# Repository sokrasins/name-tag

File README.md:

# MAKE Roanoke Name tag

A battery-powered, LED-lit "My name is" name tag for
MAKE Roanoke, designed in KiCad 9.

It is made of two stacked PCBs:

- **Back board:** holds all the electronics, including the battery, power
  switch, boost converter, brightness pot and 27 LEDs. This board provides 
  illumination to highlight the features on the front board.
- **Front board:** a plain faceplate with no parts. It has the "My name is:"
  silkscreen and a wrench graphic, and it covers the LED area of the back 
  board. The board lacks soldermask so that the wrench and the area with the 
  individual's name light up when the name tag is on.

The boards line up on four M3 mounting holes and are held together with
standoffs. A slot at the top of the back board is for a clip.

This project has been designed explicitly to be built via reflow as part of a 
class.

Viewable links are here:
- [Schematic](https://github.com/sokrasins/nametag/blob/main/docs/nametag_back_schematic_rev2.pdf)
- [Back PCB](https://pcbview.io/?github=https%3A%2F%2Fgithub.com%2Fsokrasins%2Fname-tag%2Fblob%2FHEAD%2Fpcbs%2Fnametag_back%2Fnametag_back.kicad_pcb)
- [Front PCB](https://pcbview.io/?github=https%3A%2F%2Fgithub.com%2Fsokrasins%2Fname-tag%2Fblob%2FHEAD%2Fpcbs%2Fnametag_front%2Fnametag_front.kicad_pcb)
- [Assembly](https://htmlpreview.github.io/?https://raw.githubusercontent.com/sokrasins/nametag/refs/heads/develop/docs/assembly.html)

## Renders

## How it works

- **Power:** a single AAA cell switched by an SPDT slide switch.
- **Boost converter:** a TI TPS613221A steps the cell up to a +3V3 rail.
- **LEDs:** 27× SMD LEDs (22 yellow, 5 green). Each one has a 1 kΩ
  current-limiting resistor.
- **Brightness:** all LEDs share a single BSS138 low-side MOSFET. A 10 kΩ
  Bourns TC33X trimmer potentiometer divides the 3.3 V rail and drives its
  `CTRL` gate line, so turning it dims or brightens every LED together.

## Boards

| | Back | Front |
| --- | --- | --- |
| Size | 100 × 75 mm | 100 × 53 mm |
| Layers / thickness | 2 / 1.6 mm | 2 / 1.6 mm |
| Components | All electronics | None (4× M3 holes) |

## Repository layout

| Path | Contents |
| --- | --- |
| `pcbs/nametag_back/` | Back board KiCad project (schematic and layout) |
| `pcbs/nametag_back/gerbs/` | Back board Gerbers and drill files |
| `pcbs/nametag_front/` | Front board KiCad project (layout only, no schematic) |
| `pcbs/nametag_front/gerbs/` | Front board Gerbers and drill files |
| `docs/assembly.html` | Interactive BOM for assembling the back board |
| `docs/bom.csv` | Bill of materials for the back board, with LCSC part numbers |

## Regenerating the renders, schematic PDF and interactive BOM

With KiCad 9 or newer installed, run:

```sh
scripts/render_pcbs.sh          # top side (the images above)
scripts/render_pcbs.sh both     # also writes docs/renders/*_render_bottom.png
```

It calls `kicad-cli pcb render` for each board and `kicad-cli sch export pdf`
to write `docs/nametag_back_schematic_rev<N>.pdf`, where `<N>` is the
revision from the schematic's title block. Set `KICAD_CLI` if
`kicad-cli` isn't on your `PATH`. `QUALITY`, `WIDTH`, `HEIGHT` and `BACKGROUND`
change the output.

If the [InteractiveHtmlBom](https://github.com/openscopeproject/InteractiveHtmlBom)
plugin is installed through KiCad's Plugin and Content Manager, it also writes
`docs/assembly.html`. Set `IBOM` to point at `generate_interactive_bom.py` if
the plugin lives elsewhere, and `IBOM_PYTHON` if the python that can import
KiCad's `pcbnew` module isn't found automatically.

## Open items

- The top-level schematic still has a couple of "TODO: Verify" notes.

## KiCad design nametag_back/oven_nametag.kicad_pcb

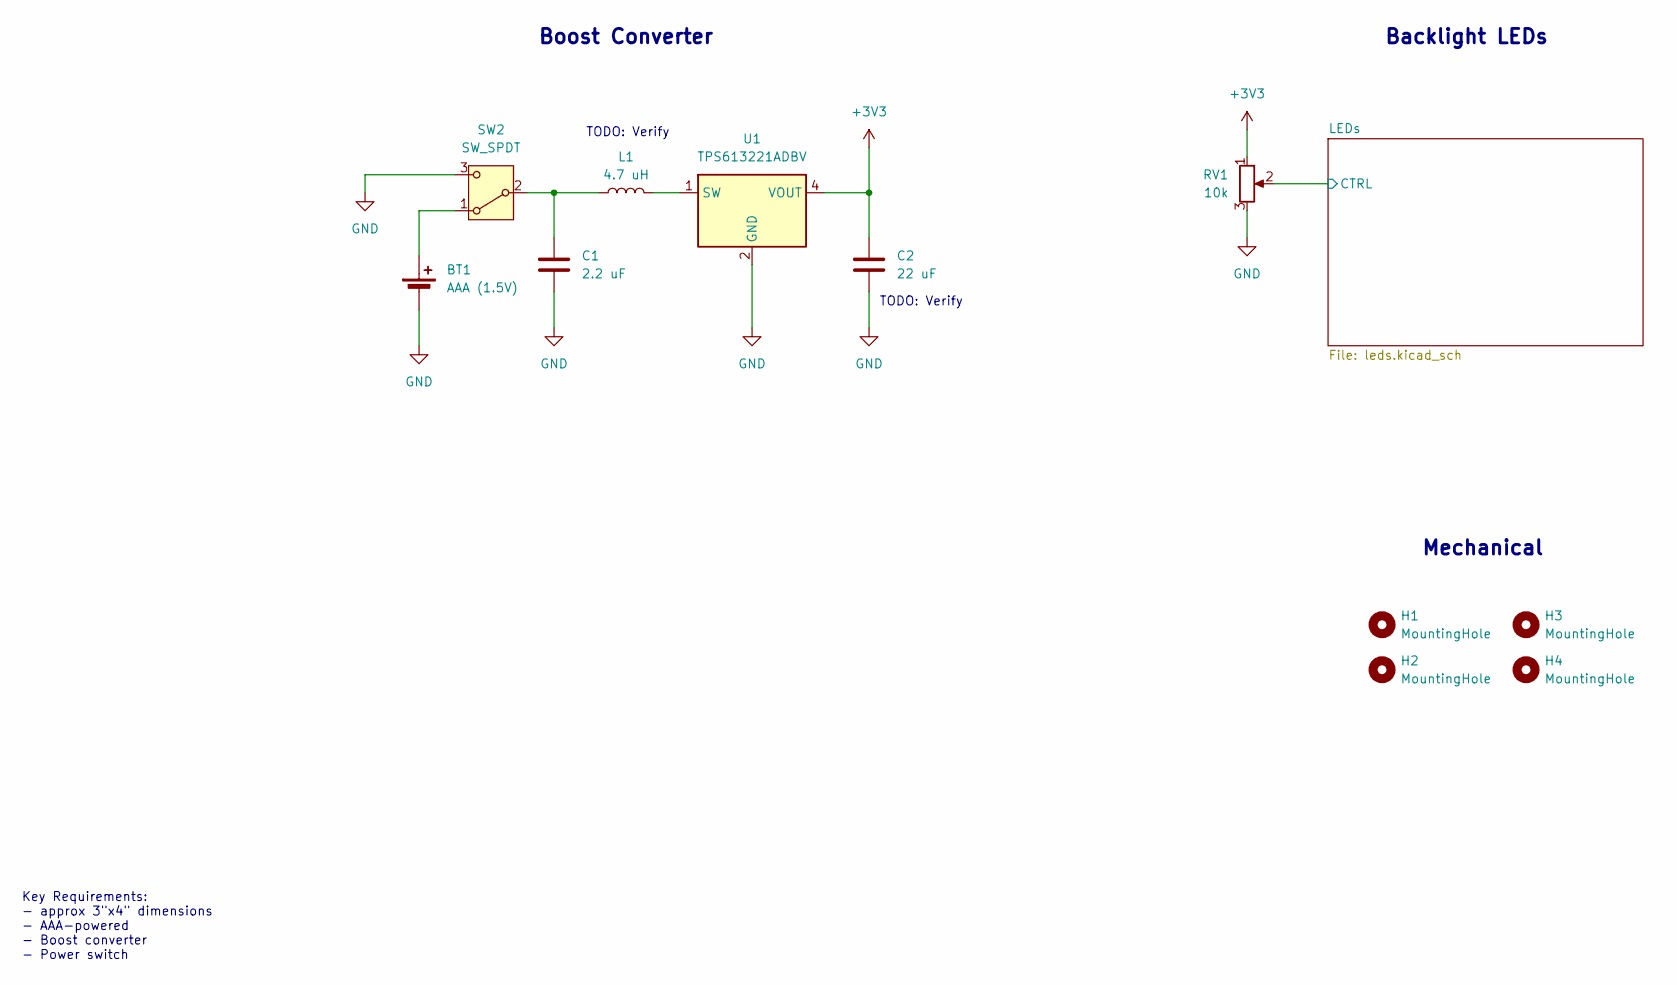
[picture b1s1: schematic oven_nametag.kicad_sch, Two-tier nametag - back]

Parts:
BT1: AAA (1.5V); BatteryHolder_Keystone_2466_1xAAA
C1: 2.2 uF; C_0805_2012Metric
C2: 22 uF; C_0805_2012Metric
H1, H2, H3, H4: MountingHole; MountingHole_3.2mm_M3
L1: 4.7 uH; L_0805_2012Metric
RV1: 10k; Potentiometer_Bourns_TC33X_Vertical
SW2: SW_SPDT; SW_SPDT_PCM12
U1: TPS613221ADBV; SOT-23-5

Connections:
+3V3: C2.1, RV1.1, U1.4 (VOUT); also elsewhere on the board
/LEDs/CTRL: RV1.2; also elsewhere on the board
GND: BT1.2 (-), C1.2, C2.2, RV1.3, SW2.3 (C), U1.2 (GND); also elsewhere on the board
unnamed: BT1.1 (+), SW2.1 (A)
unnamed: C1.1, L1.1, SW2.2 (B)
unnamed: L1.2, U1.1 (SW)

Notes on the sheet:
Backlight LEDs
TODO: Verify
Boost Converter
Key Requirements: - approx 3"x4" dimensions - AAA-powered - Boost converter - Power switch
Mechanical

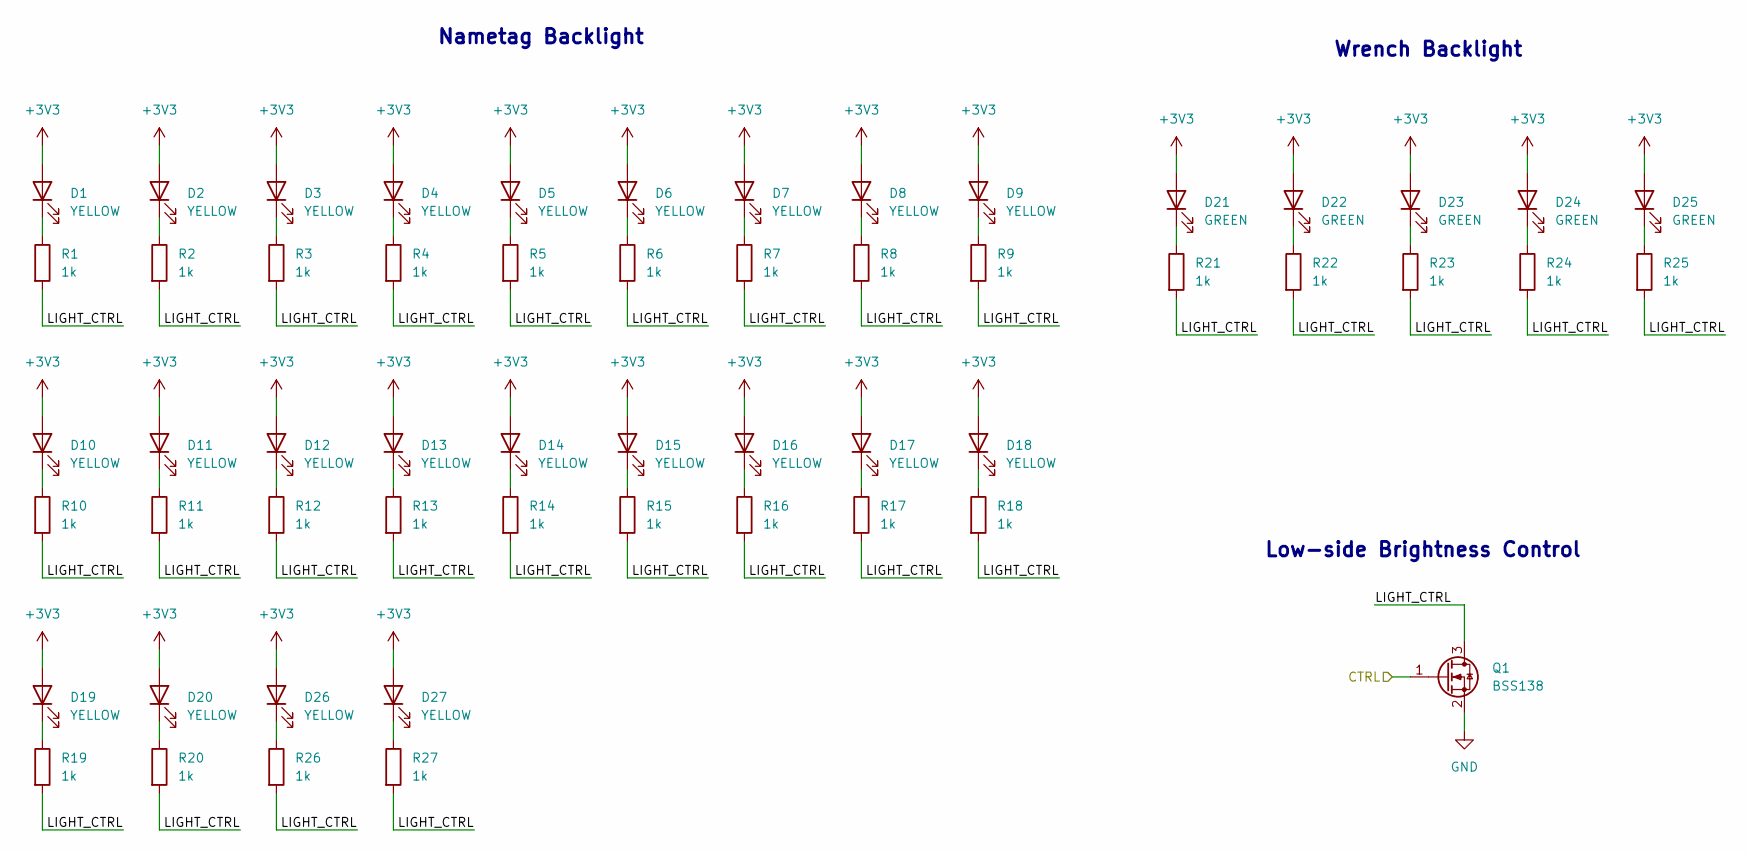
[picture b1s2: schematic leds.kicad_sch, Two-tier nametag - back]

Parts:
D1, D2, D3, D4, D5, D6, D7, D8, D9, D10, D11, D12, D13, D14, D15, D16, D17, D18, D19, D20, D26, D27: YELLOW; LED_1206_3216Metric
D21, D22, D23, D24, D25: GREEN; LED_1206_3216Metric
Q1: BSS138; SOT-23
R1, R2, R3, R4, R5, R6, R7, R8, R9, R10, R11, R12, R13, R14, R15, R16, R17, R18, R19, R20, R21, R22, R23, R24, R25, R26, R27: 1k; R_0805_2012Metric

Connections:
+3V3: D1.2 (A), D2.2 (A), D3.2 (A), D4.2 (A), D5.2 (A), D6.2 (A), D7.2 (A), D8.2 (A), D9.2 (A), D10.2 (A), D11.2 (A), D12.2 (A), D13.2 (A), D14.2 (A), D15.2 (A), D16.2 (A), D17.2 (A), D18.2 (A), D19.2 (A), D20.2 (A), D21.2 (A), D22.2 (A), D23.2 (A), D24.2 (A), D25.2 (A), D26.2 (A), D27.2 (A); also elsewhere on the board
/LEDs/CTRL: Q1.1 (G); also elsewhere on the board
/LEDs/LIGHT_CTRL: Q1.3 (D), R1.2, R2.2, R3.2, R4.2, R5.2, R6.2, R7.2, R8.2, R9.2, R10.2, R11.2, R12.2, R13.2, R14.2, R15.2, R16.2, R17.2, R18.2, R19.2, R20.2, R21.2, R22.2, R23.2, R24.2, R25.2, R26.2, R27.2
GND: Q1.2 (S); also elsewhere on the board
unnamed: D1.1 (K), R1.1
unnamed: D2.1 (K), R2.1
unnamed: D3.1 (K), R3.1
unnamed: D4.1 (K), R4.1
unnamed: D5.1 (K), R5.1
unnamed: D6.1 (K), R6.1
unnamed: D7.1 (K), R7.1
unnamed: D8.1 (K), R8.1
unnamed: D9.1 (K), R9.1
unnamed: D10.1 (K), R10.1
unnamed: D11.1 (K), R11.1
unnamed: D12.1 (K), R12.1
unnamed: D13.1 (K), R13.1
unnamed: D14.1 (K), R14.1
unnamed: D15.1 (K), R15.1
unnamed: D16.1 (K), R16.1
unnamed: D17.1 (K), R17.1
unnamed: D18.1 (K), R18.1
unnamed: D19.1 (K), R19.1
unnamed: D20.1 (K), R20.1
unnamed: D21.1 (K), R21.1
unnamed: D22.1 (K), R22.1
unnamed: D23.1 (K), R23.1
unnamed: D24.1 (K), R24.1
unnamed: D25.1 (K), R25.1
unnamed: D26.1 (K), R26.1
unnamed: D27.1 (K), R27.1

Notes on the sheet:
Nametag Backlight
Wrench Backlight
Low-side Brightness Control

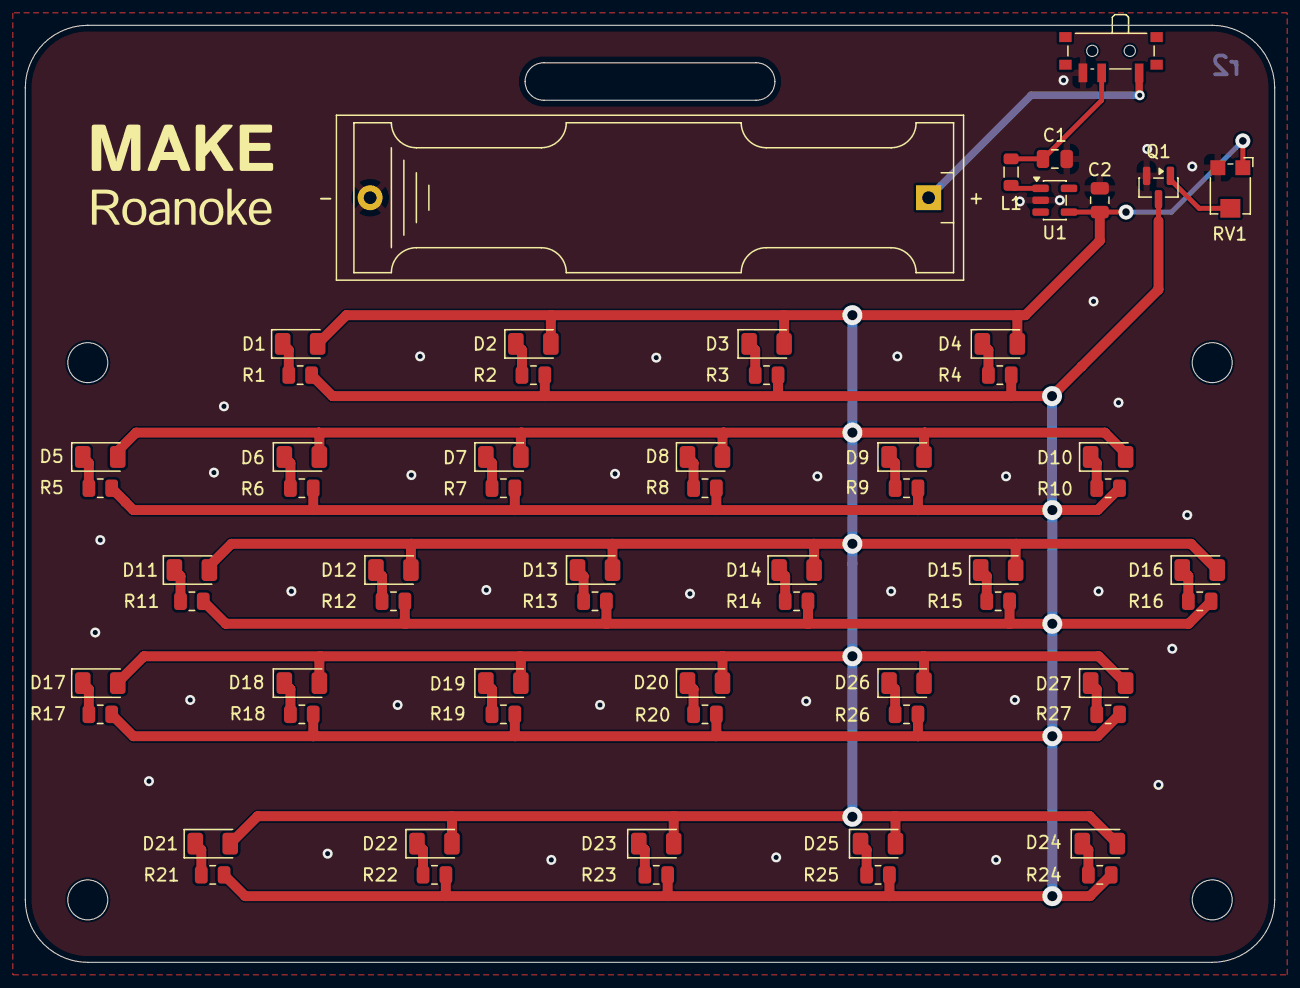
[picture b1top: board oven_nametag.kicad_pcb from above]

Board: 2 copper layers, 100.0 x 75.0 mm, 66 parts (0 on the bottom side), 34 nets.
